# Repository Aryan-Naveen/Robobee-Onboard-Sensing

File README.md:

# Robobee-Onboard-Sensing

## Utilized Components

6DOF IMU (ICM 42688-V):
https://invensense.tdk.com/products/motion-tracking/6-axis/icm-42688-v/

Time of Flight Sensor (CH-101):
https://invensense.tdk.com/products/ch101/

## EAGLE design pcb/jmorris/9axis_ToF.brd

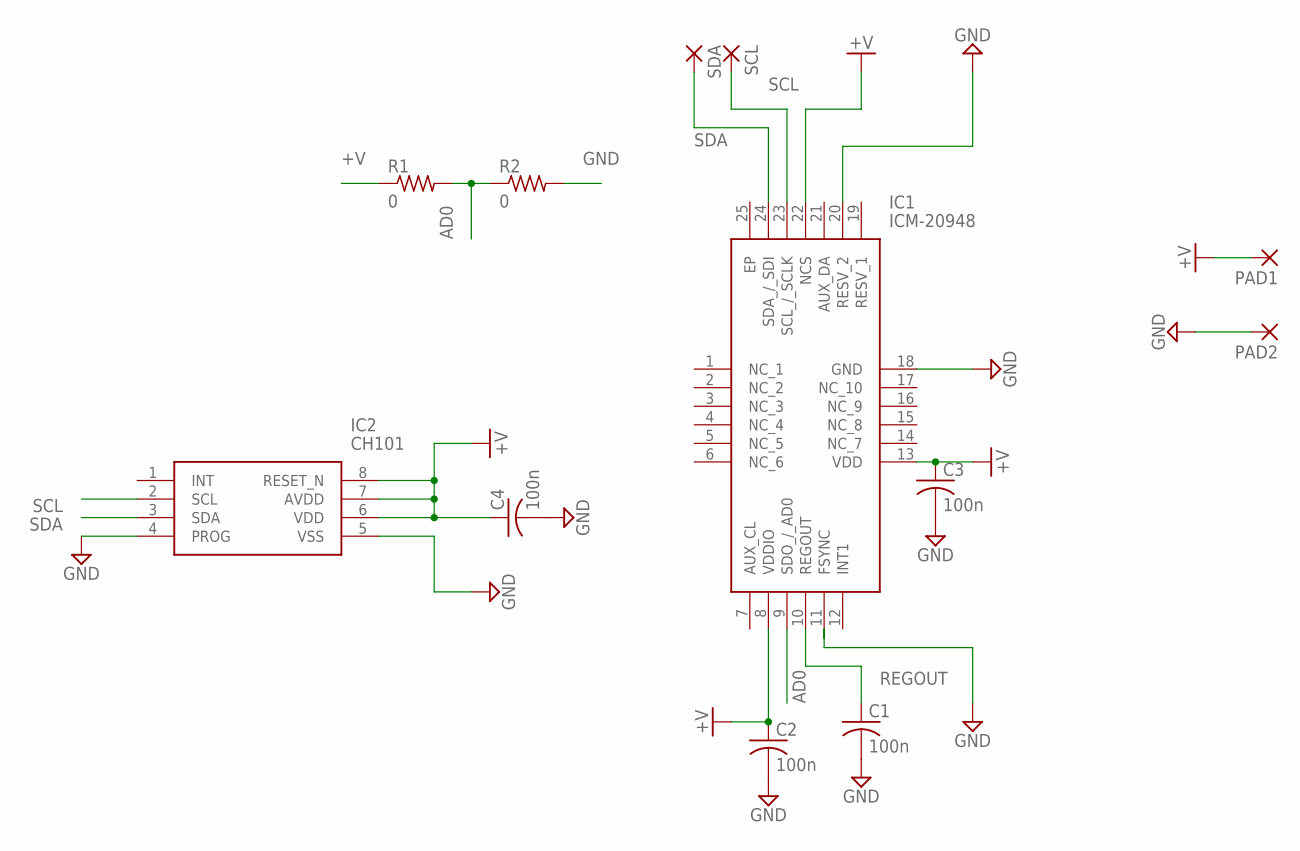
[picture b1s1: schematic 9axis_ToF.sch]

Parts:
C1, C2, C3, C4: 100n; C0603
IC1: ICM-20948; QFN40P300X300X105-25N
IC2: CH101
PAD1, PAD2: SMD5; SMD2,54-5,08
R1, R2: 0; R0603
SCL: SMD5; SMD2,54-5,08
SDA: SMD5; SMD2,54-5,08

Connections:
+V: C2.1, C3.1, C4.1, IC1.8 (VDDIO), IC1.13 (VDD), IC1.22 (NCS), IC2.6 (VDD), IC2.7 (AVDD), IC2.8 (RESET_N), PAD1.1, R1.1
AD0: IC1.9 (SDO_/_AD0), R1.2, R2.1
GND: C1.2, C2.2, C3.2, C4.2, IC1.11 (FSYNC), IC1.18 (GND), IC1.20 (RESV_2), IC2.4 (PROG), IC2.5 (VSS), PAD2.1, R2.2
REGOUT: C1.1, IC1.10 (REGOUT)
SCL: IC1.23 (SCL_/_SCLK), IC2.2 (SCL), SCL.1
SDA: IC1.24 (SDA_/_SDI), IC2.3 (SDA), SDA.1

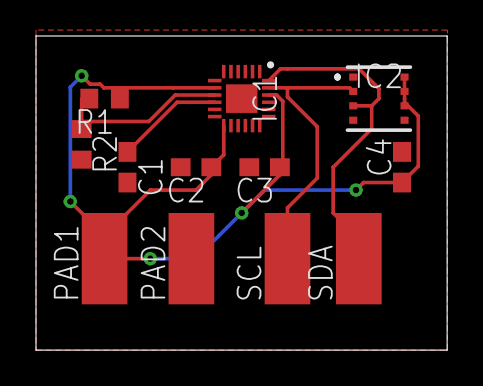
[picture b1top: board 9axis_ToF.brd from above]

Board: 2 copper layers, 22.8 x 17.4 mm, 12 parts (0 on the bottom side), 6 nets.

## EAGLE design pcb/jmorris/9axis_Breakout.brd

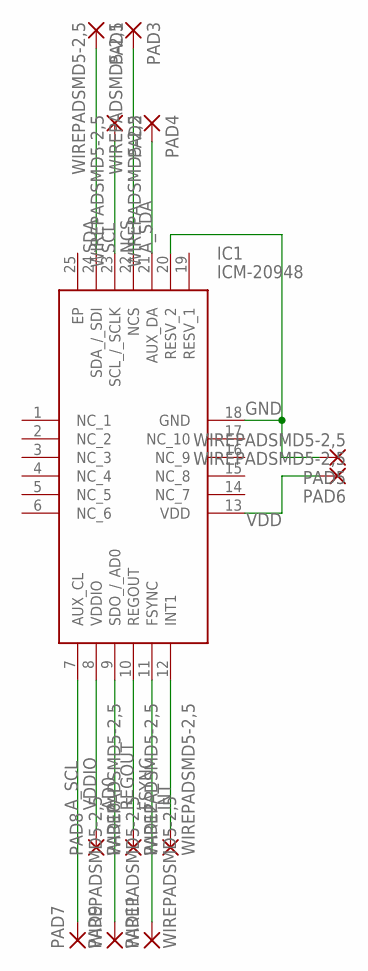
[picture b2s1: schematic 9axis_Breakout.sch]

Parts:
IC1: ICM-20948; QFN40P300X300X105-25N
PAD1, PAD2, PAD3, PAD4, PAD5, PAD6, PAD7, PAD8, PAD9, PAD10, PAD11, PAD12: WIREPADSMD5-2,5; 5-2,5

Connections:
AD0: IC1.9 (SDO_/_AD0), PAD9.1
A_SCL: IC1.7 (AUX_CL), PAD7.1
A_SDA: IC1.21 (AUX_DA), PAD4.1
FSYNC: IC1.11 (FSYNC), PAD11.1
GND: IC1.18 (GND), IC1.20 (RESV_2), PAD5.1
INT: IC1.12 (INT1), PAD12.1
NCS: IC1.22 (NCS), PAD3.1
REGOUT: IC1.10 (REGOUT), PAD10.1
SCL: IC1.23 (SCL_/_SCLK), PAD2.1
SDA: IC1.24 (SDA_/_SDI), PAD1.1
VDD: IC1.13 (VDD), PAD6.1
VDDIO: IC1.8 (VDDIO), PAD8.1

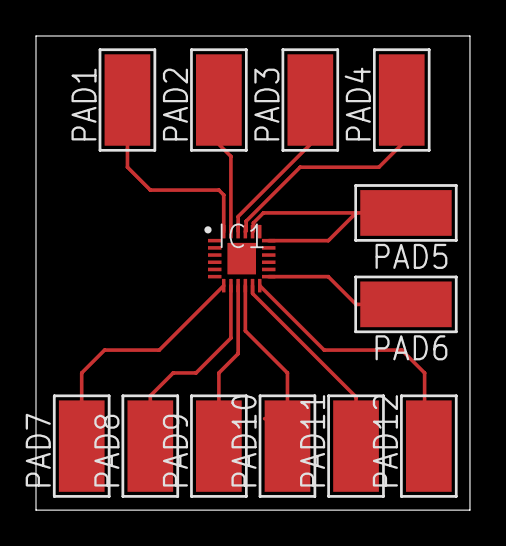
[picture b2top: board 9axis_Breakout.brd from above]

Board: 2 copper layers, 24.1 x 26.3 mm, 13 parts (0 on the bottom side), 12 nets.

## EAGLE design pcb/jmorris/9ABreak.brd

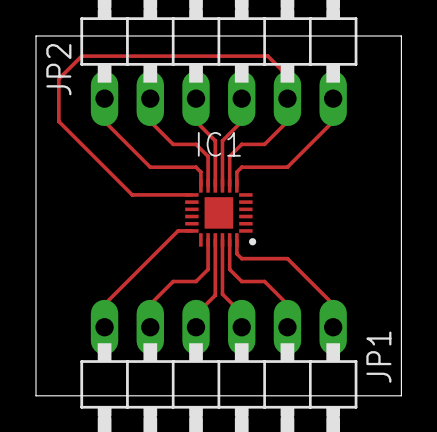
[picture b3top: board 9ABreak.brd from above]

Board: 2 copper layers, 20.3 x 20.0 mm, 3 parts (0 on the bottom side), 12 nets.

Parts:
IC1: ICM-20948; QFN40P300X300X105-25N
JP1, JP2: 1X06/90

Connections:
unnamed: IC1.7, JP2.6
unnamed: IC1.8, IC1.13, JP2.5
unnamed: IC1.9, JP2.4
unnamed: IC1.10, JP2.3
unnamed: IC1.11, JP2.2
unnamed: IC1.12, JP2.1
unnamed: IC1.24, JP1.1
unnamed: IC1.23, JP1.2
unnamed: IC1.22, JP1.3
unnamed: IC1.21, JP1.4
unnamed: IC1.20, JP1.5
unnamed: IC1.18, JP1.6

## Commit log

2023-02-25 Eagle Library Dependencies
    Dependencies
2023-03-07 Breakout and 9axis board
2023-03-24 Ino and ch101 driver
2023-03-24 oOOoOoOOooo
2023-03-31 New code is under Ino/ch101_driver/ch101_new
2023-04-01 More debugging
2023-04-18 EKF initial implementation
2023-04-19 filtering results
2023-05-01 testing script
2024-04-17 ch101 code
2024-04-17 Clean up and other ToF
2024-04-17 More additions
